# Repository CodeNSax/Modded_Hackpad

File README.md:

# The Saxpad™
This is the repo for my Saxpad™, a test project to learn a bit before commiting to the R.A.P. It was my first time to ever do something like this, and took me a long time, but I'm proud of it.
It is a shortcut pad with a bare-bones design to show off all the (very cool) internals.

****THE FINISHED PRODUCT!!!****

**INTERNALS:**
My Hackpad features a 3d printed case for the PCB that houses a XIAO-RP2040-DIP for the microcontroller, MX-Style switches for the keyboard switches, a rotary encoder switch for adjusting things with a knob, and some SK6812MINI LEDs as the backlit RGB.

**BILL OF MATERIALS:**
| Reference          | Qty | Value                                                                  | URL (If applicable)                                                                                                                                                                                                                                                                                                                                                                            | Exclude from Board | Footprint                                                     | Datasheet                                                                                                                                                                                                                                                                                                                                                                                                    |
| ------------------ | --- | ---------------------------------------------------------------------- | ---------------------------------------------------------------------------------------------------------------------------------------------------------------------------------------------------------------------------------------------------------------------------------------------------------------------------------------------------------------------------------------------- | ------------------ | ------------------------------------------------------------- | ------------------------------------------------------------------------------------------------------------------------------------------------------------------------------------------------------------------------------------------------------------------------------------------------------------------------------------------------------------------------------------------------------------ |
| D1,D2,D3,D4        | 4   | SK6812MINI                                                             |                                                                                                                                                                                                                                                                                                                                                                                                |                    | LED_SMD:LED_SK6812MINI_PLCC4_3.5x3.5mm_P1.75mm                | [https://cdn-shop.adafruit.com/product-files/2686/SK6812MINI_REV.01-1-2.pdf](https://cdn-shop.adafruit.com/product-files/2686/SK6812MINI_REV.01-1-2.pdf)                                                                                                                                                                                                                                                     |
| (Not in schematic) | 1   | Rotary Encoder Switch Knob (3 pieces)                                  |                                                                                                                                                                                                                                                                                                                                                                                                |                    | (Not in schematic)                                            | [https://www.alibaba.com/product-detail/Rotary-15mm-High-17mm-Aluminum-Shell_60628365487.html?spm=a2700.galleryofferlist.normal_offer.d_image.596b13a07ZdWbL&priceId=b9b46d351eb74acaa07c5dc284613b05](https://www.alibaba.com/product-detail/Rotary-15mm-High-17mm-Aluminum-Shell_60628365487.html?spm=a2700.galleryofferlist.normal_offer.d_image.596b13a07ZdWbL&priceId=b9b46d351eb74acaa07c5dc284613b05) |
| SW12               | 1   | RotaryEncoder_Switch                                                   |                                                                                                                                                                                                                                                                                                                                                                                                |                    | Rotary_Encoder:RotaryEncoder_Alps_EC11E-Switch_Vertical_H20mm | ~                                                                                                                                                                                                                                                                                                                                                                                                            |
| S1,S2,S3,S4        | 4   | MX-Style switches (Keyswitch)                                          |                                                                                                                                                                                                                                                                                                                                                                                                |                    | Button_Switch_Keyboard:SW_Cherry_MX_1.00u_PCB                 | ~                                                                                                                                                                                                                                                                                                                                                                                                            |
| (Not in schematic) | 4   | White Blank DSA keycaps                                                |                                                                                                                                                                                                                                                                                                                                                                                                |                    | (Not in schematic)                                            | ~                                                                                                                                                                                                                                                                                                                                                                                                            |
| U1                 | 1   | XIAO-RP2040-DIP                                                        |                                                                                                                                                                                                                                                                                                                                                                                                |                    | Seeed Studio XIAO Series Library:XIAO-RP2040-DIP              |                                                                                                                                                                                                                                                                                                                                                                                                              |
| (Not in schematic) | 1   | 3D Printed Case (2 parts, top and bottom case, sunset yellow prefered) |                                                                                                                                                                                                                                                                                                                                                                                                |                    | (not in schematic)                                            |                                                                                                                                                                                                                                                                                                                                                                                                              |
| (Not in schematic) | 1   | Rotary Encoder Knob                                                    | [https://www.alibaba.com/product-detail/Rotary-15mm-High-17mm-Aluminum-Shell_60628365487.html?spm=a2700.prosearch.normal_offer.d_image.418b67afe6qmXm&priceId=c14037a39e5f47468279b33e913a76cb](https://www.alibaba.com/product-detail/Rotary-15mm-High-17mm-Aluminum-Shell_60628365487.html?spm=a2700.prosearch.normal_offer.d_image.418b67afe6qmXm&priceId=c14037a39e5f47468279b33e913a76cb) |                    | (Not in Schematic)                                            |                                                                                                                                                                                                                                                                                                                                                                                                              |

***And the screenshots...***

SCHEMATIC:

PCB:

CASE:

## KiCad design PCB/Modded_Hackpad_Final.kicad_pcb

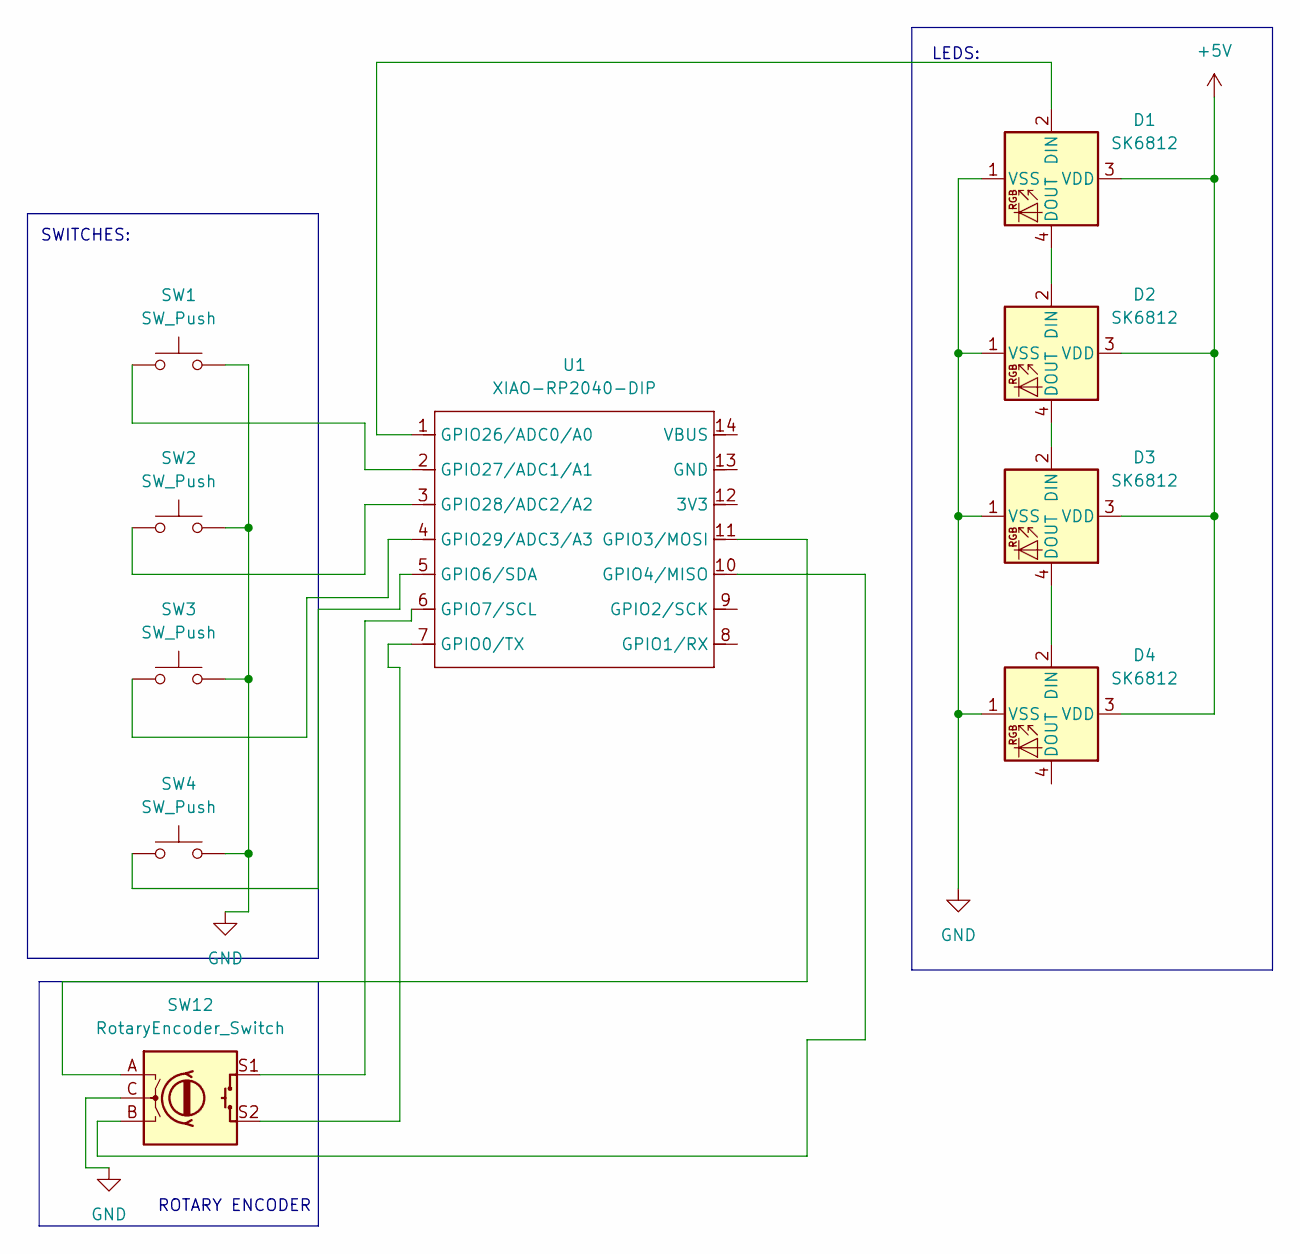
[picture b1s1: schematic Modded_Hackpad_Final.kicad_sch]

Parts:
D1, D2, D3, D4: SK6812; LED_SK6812MINI_PLCC4_3.5x3.5mm_P1.75mm
SW1, SW2, SW3, SW4: SW_Push; SW_Cherry_MX_1.00u_PCB
SW12: RotaryEncoder_Switch; RotaryEncoder_Alps_EC11E-Switch_Vertical_H20mm
U1: XIAO-RP2040-DIP

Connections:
+5V: D1.3 (VDD), D2.3 (VDD), D3.3 (VDD), D4.3 (VDD)
GND: D1.1 (VSS), D2.1 (VSS), D3.1 (VSS), D4.1 (VSS), SW1.2, SW2.2, SW3.2, SW4.2, SW12.C
unnamed: D1.2 (DIN), U1.1 (GPIO26/ADC0/A0)
unnamed: D1.4 (DOUT), D2.2 (DIN)
unnamed: D2.4 (DOUT), D3.2 (DIN)
unnamed: D3.4 (DOUT), D4.2 (DIN)
unnamed: SW12.S2, U1.7 (GPIO0/TX)
unnamed: SW12.A, U1.11 (GPIO3/MOSI)
unnamed: SW12.B, U1.10 (GPIO4/MISO)
unnamed: SW4.1, U1.5 (GPIO6/SDA)
unnamed: SW12.S1, U1.6 (GPIO7/SCL)
unnamed: SW1.1, U1.2 (GPIO27/ADC1/A1)
unnamed: SW2.1, U1.3 (GPIO28/ADC2/A2)
unnamed: SW3.1, U1.4 (GPIO29/ADC3/A3)

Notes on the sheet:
SWITCHES:
LEDS:
ROTARY ENCODER

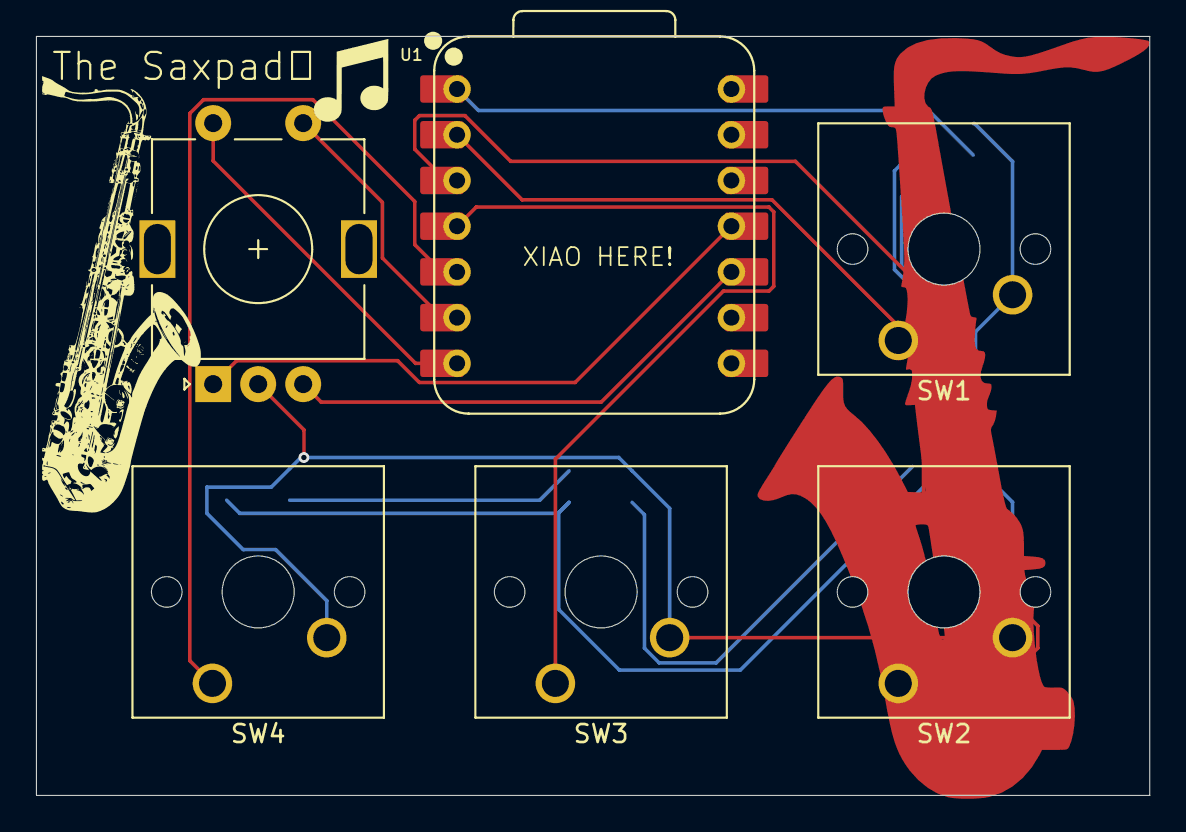
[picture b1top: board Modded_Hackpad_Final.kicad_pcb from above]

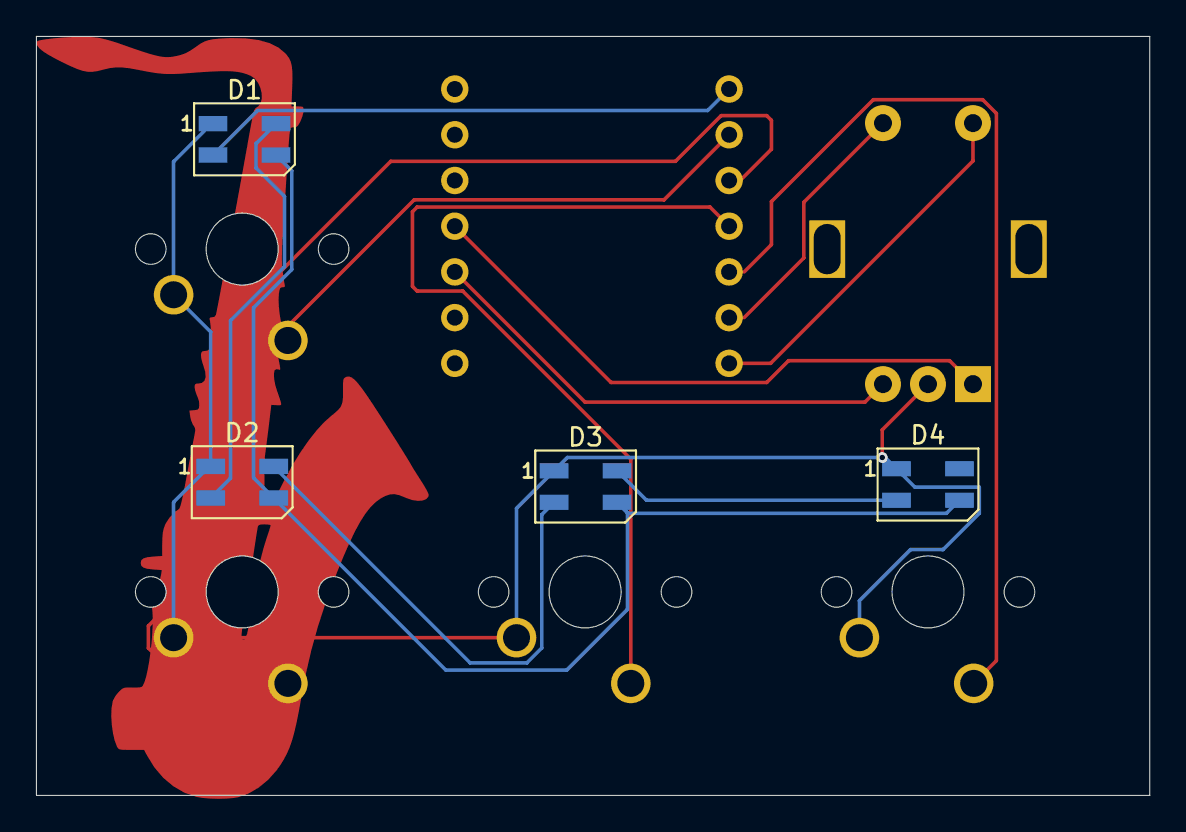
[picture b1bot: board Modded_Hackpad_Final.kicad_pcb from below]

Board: 2 copper layers, 61.8 x 42.2 mm, 10 parts (4 on the bottom side), 14 nets.

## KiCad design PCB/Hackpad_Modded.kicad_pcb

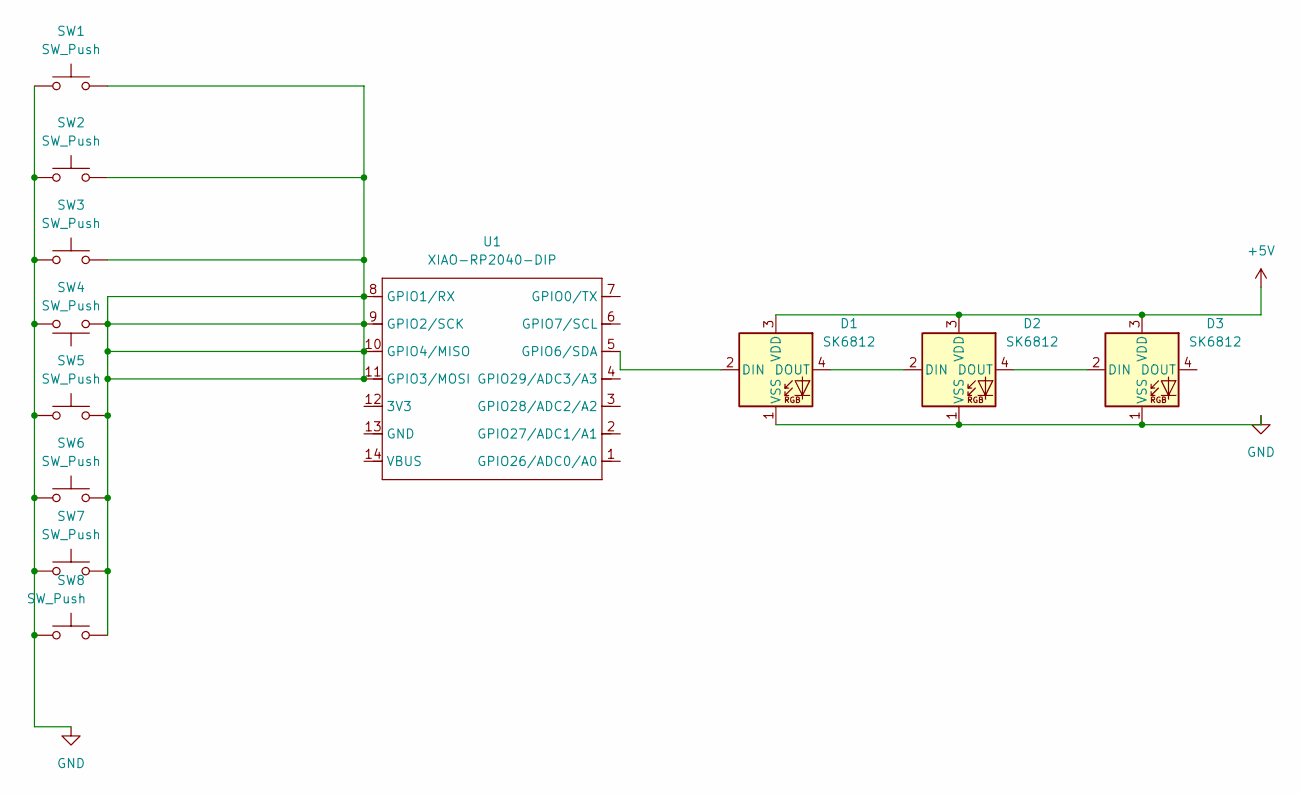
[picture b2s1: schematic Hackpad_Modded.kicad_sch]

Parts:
D1, D2, D3: SK6812; LED_SK6812MINI_PLCC4_3.5x3.5mm_P1.75mm
SW1, SW2, SW3, SW4, SW5, SW6, SW7, SW8: SW_Push; SW_Cherry_MX_1.00u_PCB
U1: XIAO-RP2040-DIP

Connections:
+5V: D1.3 (VDD), D2.3 (VDD), D3.3 (VDD)
GND: D1.1 (VSS), D2.1 (VSS), D3.1 (VSS), SW1.1, SW2.1, SW3.1, SW4.2, SW5.1, SW6.1, SW7.1, SW8.1
unnamed: D1.2 (DIN), U1.5 (GPIO6/SDA)
unnamed: D1.4 (DOUT), D2.2 (DIN)
unnamed: D2.4 (DOUT), D3.2 (DIN)
unnamed: SW1.2, SW2.2, SW3.2, SW4.1, SW5.2, SW6.2, SW7.2, SW8.2, U1.8 (GPIO1/RX), U1.9 (GPIO2/SCK), U1.10 (GPIO4/MISO), U1.11 (GPIO3/MOSI)

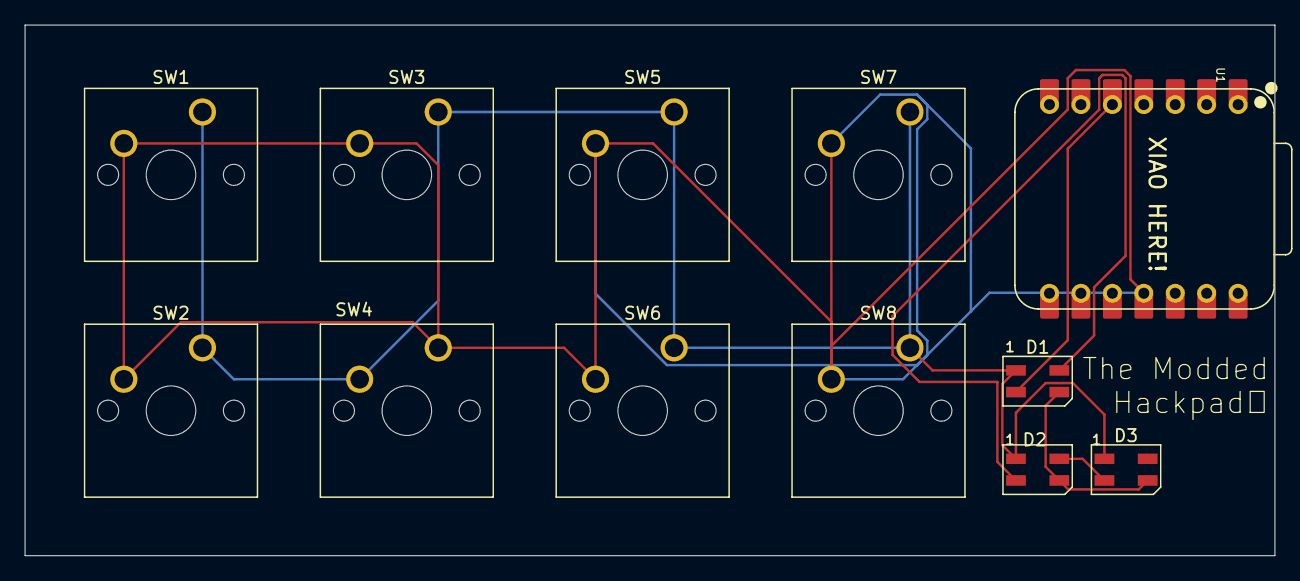
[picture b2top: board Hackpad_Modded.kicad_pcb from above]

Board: 2 copper layers, 101.0 x 42.9 mm, 12 parts (0 on the bottom side), 6 nets.

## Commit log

2026-02-01 Update PCB image in README
    Replaced PCB image with a new screenshot.
2026-02-07 Fix formatting and remove duplicate image in README
    Removed duplicate image tag and cleaned up formatting.
2026-02-08 sfdfs
2026-02-08 Replace schematic image URL in README
    Updated schematic image in README with a new link.
2026-02-08 Add rotary encoder switch knob to BOM
2026-02-08 Refactor Bill of Materials in README
    Updated the Bill of Materials section with improved formatting and added URLs for components.
